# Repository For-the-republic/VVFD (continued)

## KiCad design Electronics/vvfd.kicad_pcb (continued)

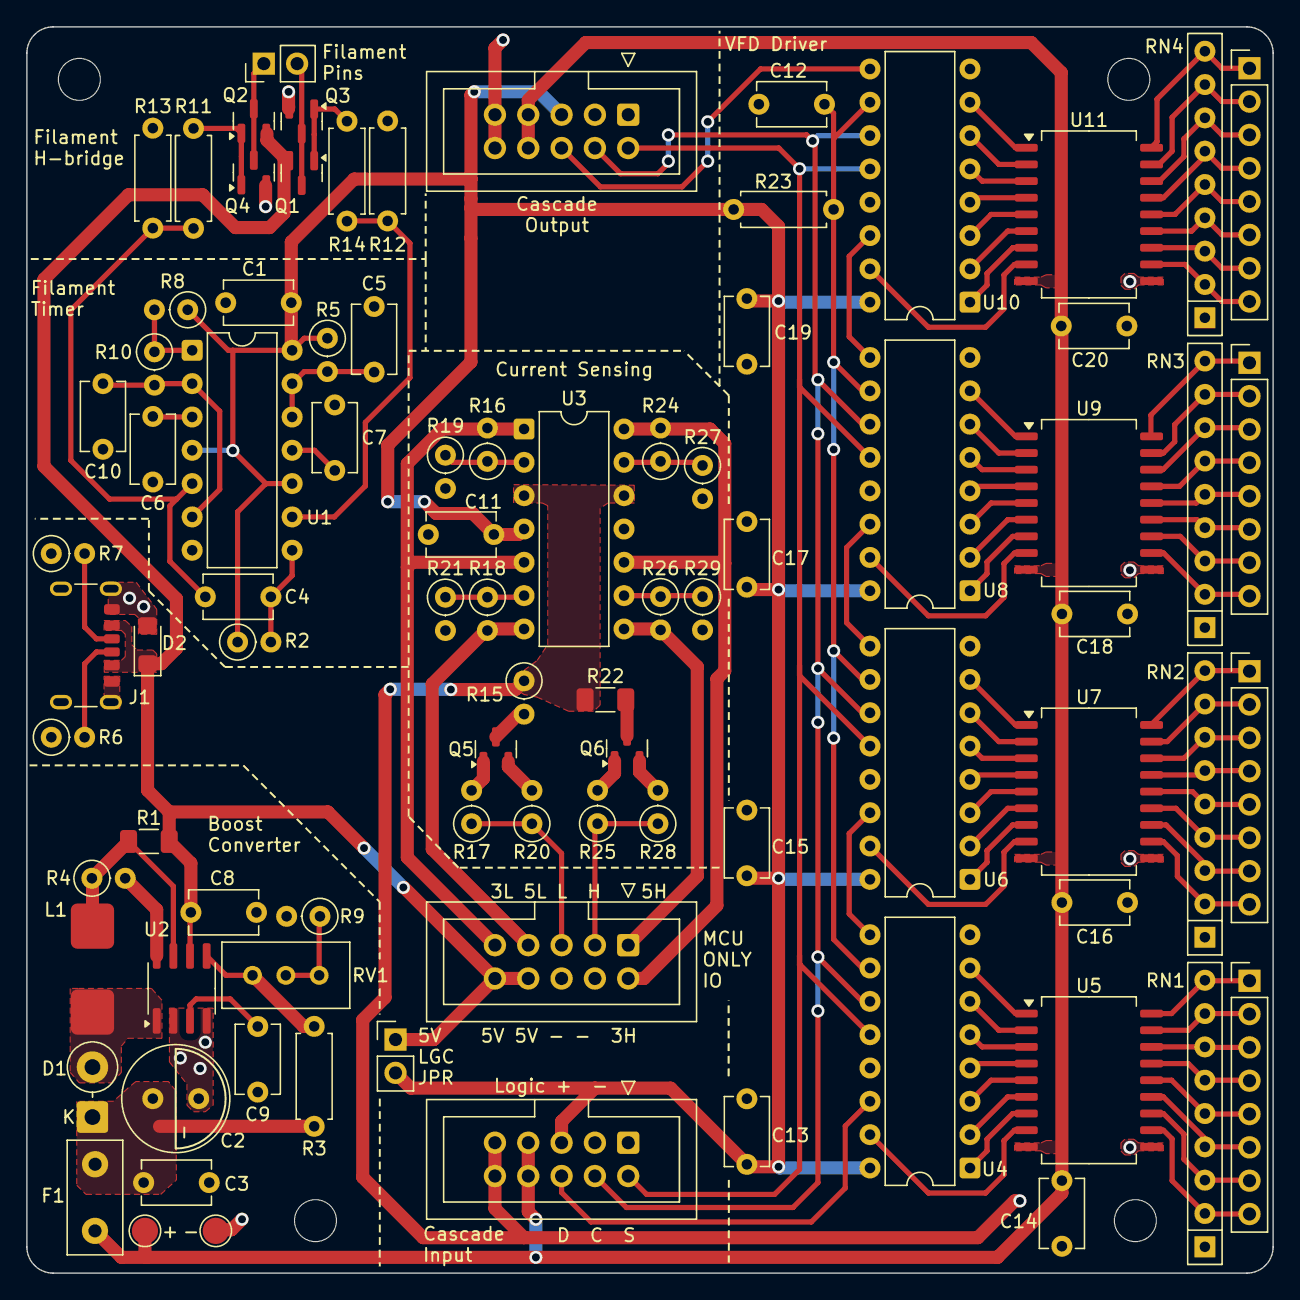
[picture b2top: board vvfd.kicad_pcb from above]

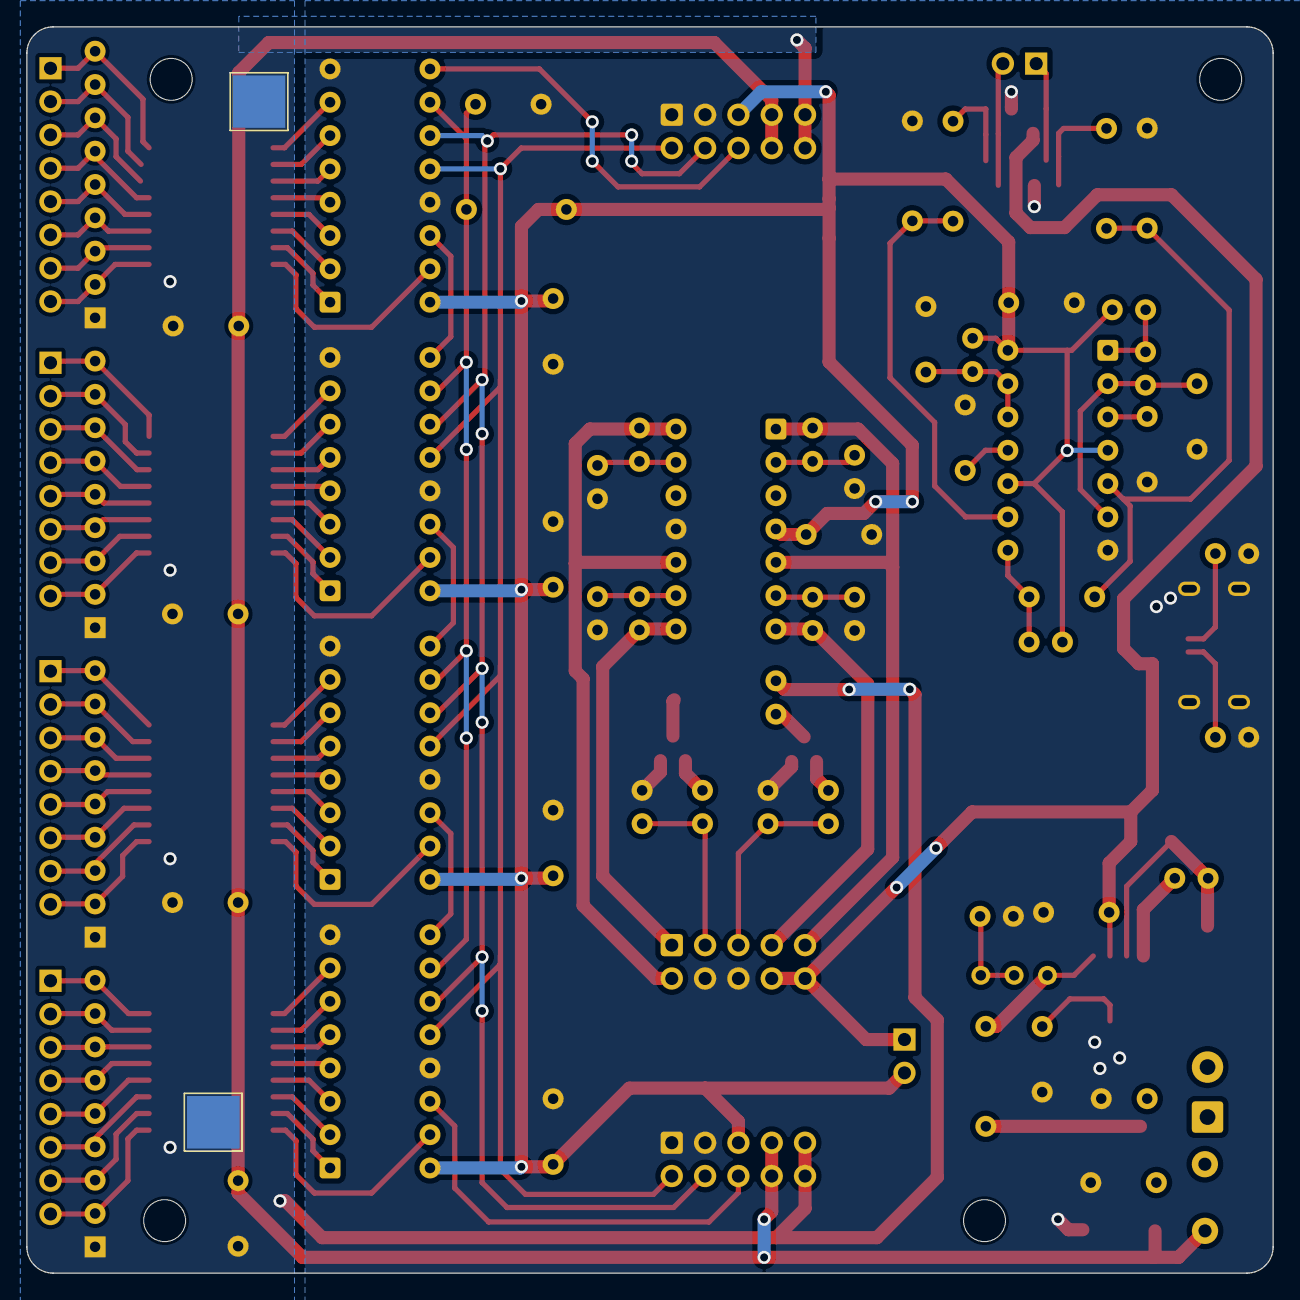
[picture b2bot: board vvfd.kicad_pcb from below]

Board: 2 copper layers, 95.0 x 95.0 mm, 93 parts (2 on the bottom side), 112 nets.

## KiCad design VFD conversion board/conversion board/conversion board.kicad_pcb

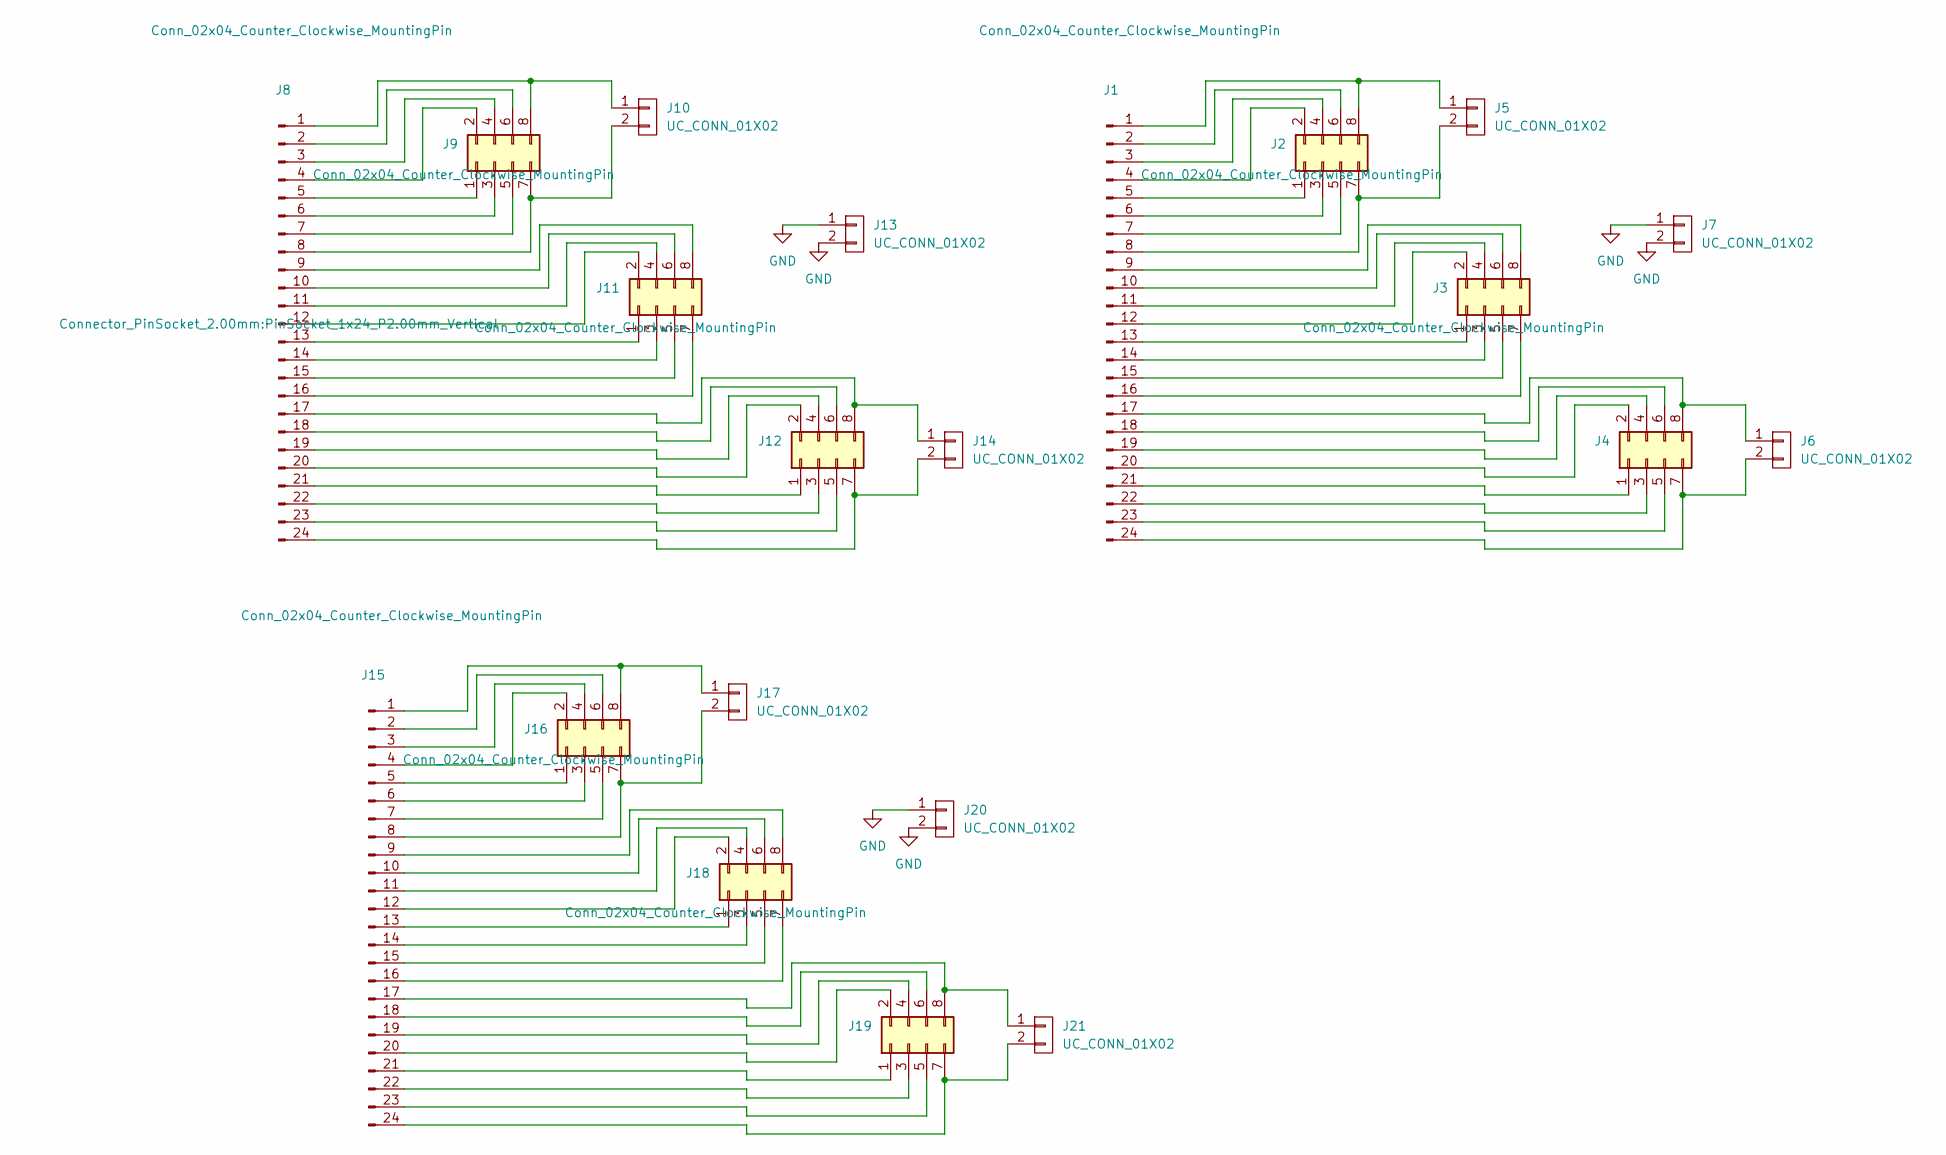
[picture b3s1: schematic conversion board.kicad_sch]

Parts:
J1, J8, J15: Conn_01x24_Pin; PinSocket_1x24_P2.00mm_Vertical
J2, J3, J4, J9, J11, J12, J16, J18, J19: Conn_02x04_Counter_Clockwise_MountingPin; PinHeader_2x04_P2.54mm_Vertical
J5, J6, J7, J10, J13, J14, J17, J20, J21: UC_CONN_01X02; PinHeader_1x02_P2.54mm_Vertical

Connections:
GND: J7.1, J7.2, J13.1, J13.2, J20.1, J20.2
unnamed: J1.1, J2.8, J5.1
unnamed: J1.2, J2.6
unnamed: J1.3, J2.4
unnamed: J1.4, J2.2
unnamed: J1.5, J2.1
unnamed: J1.6, J2.3
unnamed: J1.7, J2.5
unnamed: J1.8, J2.7, J5.2
unnamed: J1.9, J3.8
unnamed: J1.10, J3.6
unnamed: J1.11, J3.4
unnamed: J1.12, J3.2
unnamed: J1.13, J3.1
unnamed: J1.14, J3.3
unnamed: J1.15, J3.5
unnamed: J1.16, J3.7
unnamed: J1.17, J4.8, J6.1
unnamed: J1.18, J4.6
unnamed: J1.19, J4.4
unnamed: J1.20, J4.2
unnamed: J1.21, J4.1
unnamed: J1.22, J4.3
unnamed: J1.23, J4.5
unnamed: J1.24, J4.7, J6.2
unnamed: J8.2, J9.6
unnamed: J8.3, J9.4
unnamed: J8.4, J9.2
unnamed: J8.5, J9.1
unnamed: J8.6, J9.3
unnamed: J8.7, J9.5
unnamed: J8.1, J9.8, J10.1
unnamed: J8.8, J9.7, J10.2
unnamed: J8.13, J11.1
unnamed: J8.12, J11.2
unnamed: J8.14, J11.3
unnamed: J8.11, J11.4
unnamed: J8.15, J11.5
unnamed: J8.10, J11.6
unnamed: J8.16, J11.7
unnamed: J8.9, J11.8
unnamed: J8.21, J12.1
unnamed: J8.20, J12.2
unnamed: J8.22, J12.3
unnamed: J8.19, J12.4
unnamed: J8.23, J12.5
unnamed: J8.18, J12.6
unnamed: J8.24, J12.7, J14.2
unnamed: J8.17, J12.8, J14.1
unnamed: J15.1, J16.8, J17.1
unnamed: J15.2, J16.6
unnamed: J15.3, J16.4
unnamed: J15.4, J16.2
unnamed: J15.5, J16.1
unnamed: J15.6, J16.3
unnamed: J15.7, J16.5
unnamed: J15.8, J16.7, J17.2
unnamed: J15.9, J18.8
unnamed: J15.10, J18.6
unnamed: J15.11, J18.4
unnamed: J15.12, J18.2
unnamed: J15.13, J18.1
unnamed: J15.14, J18.3
unnamed: J15.15, J18.5
unnamed: J15.16, J18.7
unnamed: J15.17, J19.8, J21.1
unnamed: J15.18, J19.6
unnamed: J15.19, J19.4
unnamed: J15.20, J19.2
unnamed: J15.21, J19.1
unnamed: J15.22, J19.3
unnamed: J15.23, J19.5
unnamed: J15.24, J19.7, J21.2

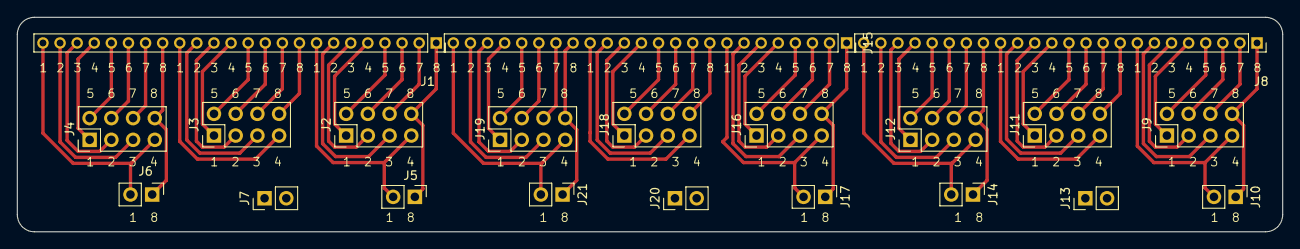
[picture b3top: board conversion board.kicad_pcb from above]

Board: 2 copper layers, 148.0 x 25.1 mm, 21 parts (0 on the bottom side), 73 nets.

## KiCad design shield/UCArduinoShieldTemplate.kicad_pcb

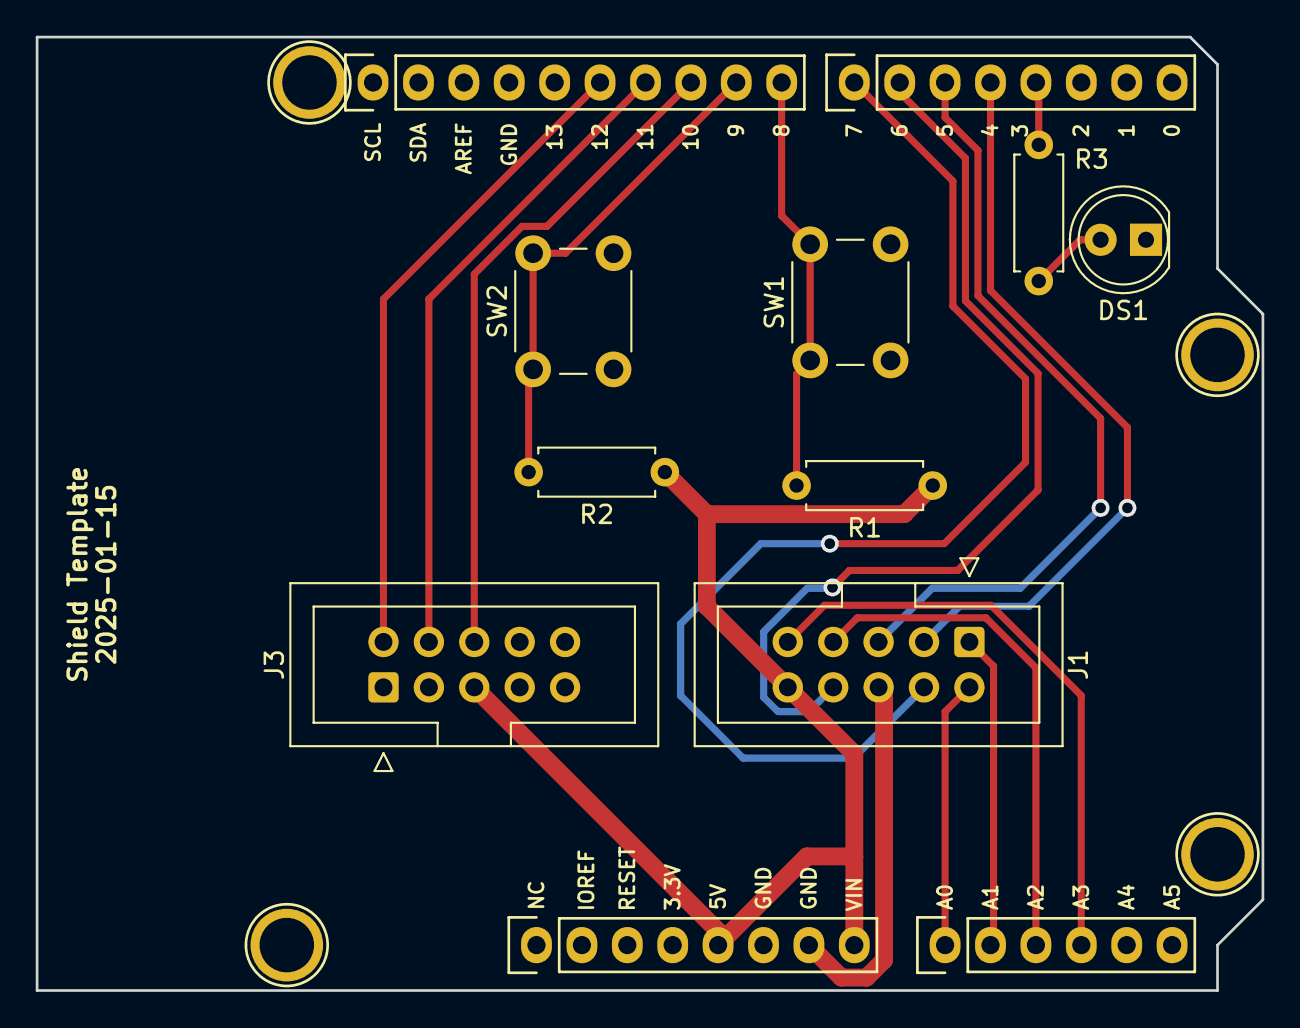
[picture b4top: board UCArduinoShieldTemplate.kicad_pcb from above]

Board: 2 copper layers, 68.6 x 53.3 mm, 16 parts (0 on the bottom side), 17 nets.

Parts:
DS1: UC_LED; LED_D5.0mm
H1, H2, H3, H4: CONN_01X01; Mounting_Hole
J1, J3: Conn_02x05_Counter_Clockwise; IDC-Header_2x05_P2.54mm_Vertical
P1: Power; Socket_Strip_Arduino_1x08
P2: Analog; Socket_Strip_Arduino_1x06
P3: Digital; Socket_Strip_Arduino_1x10
P4: Digital; Socket_Strip_Arduino_1x08
R1, R2, R3: 1k; R_Axial_DIN0207_L6.3mm_D2.5mm_P7.62mm_Horizontal
SW1, SW2: UC_SW_Push; SW_PUSH_6mm_H5mm

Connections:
3HCS: J1.2, P2.1
3LCS: J1.9, P2.4
5HCS: J1.1, P2.2
5LCS: J1.7, P2.3
+5V: J1.10, J3.5, P1.5, P1.8, R1.1, R2.1
BONE: P3.10, R1.2, SW1.1
BTWO: P3.9, R2.2, SW2.1
CLK: J3.4, P3.7
GND: DS1.1 (K), J1.6, J3.1, J3.3, P1.6, P1.7, P3.4, SW1.2, SW2.2
H1: J1.8, P4.2
H2: J1.4, P4.1
HCS_EN: J1.3, P4.4
LCS_EN: J1.5, P4.3
MAIN_SER_OUT: J3.6, P3.8
unnamed: DS1.2 (A), R3.2
SYNC: J3.2, P3.6
indicator: P4.5, R3.1

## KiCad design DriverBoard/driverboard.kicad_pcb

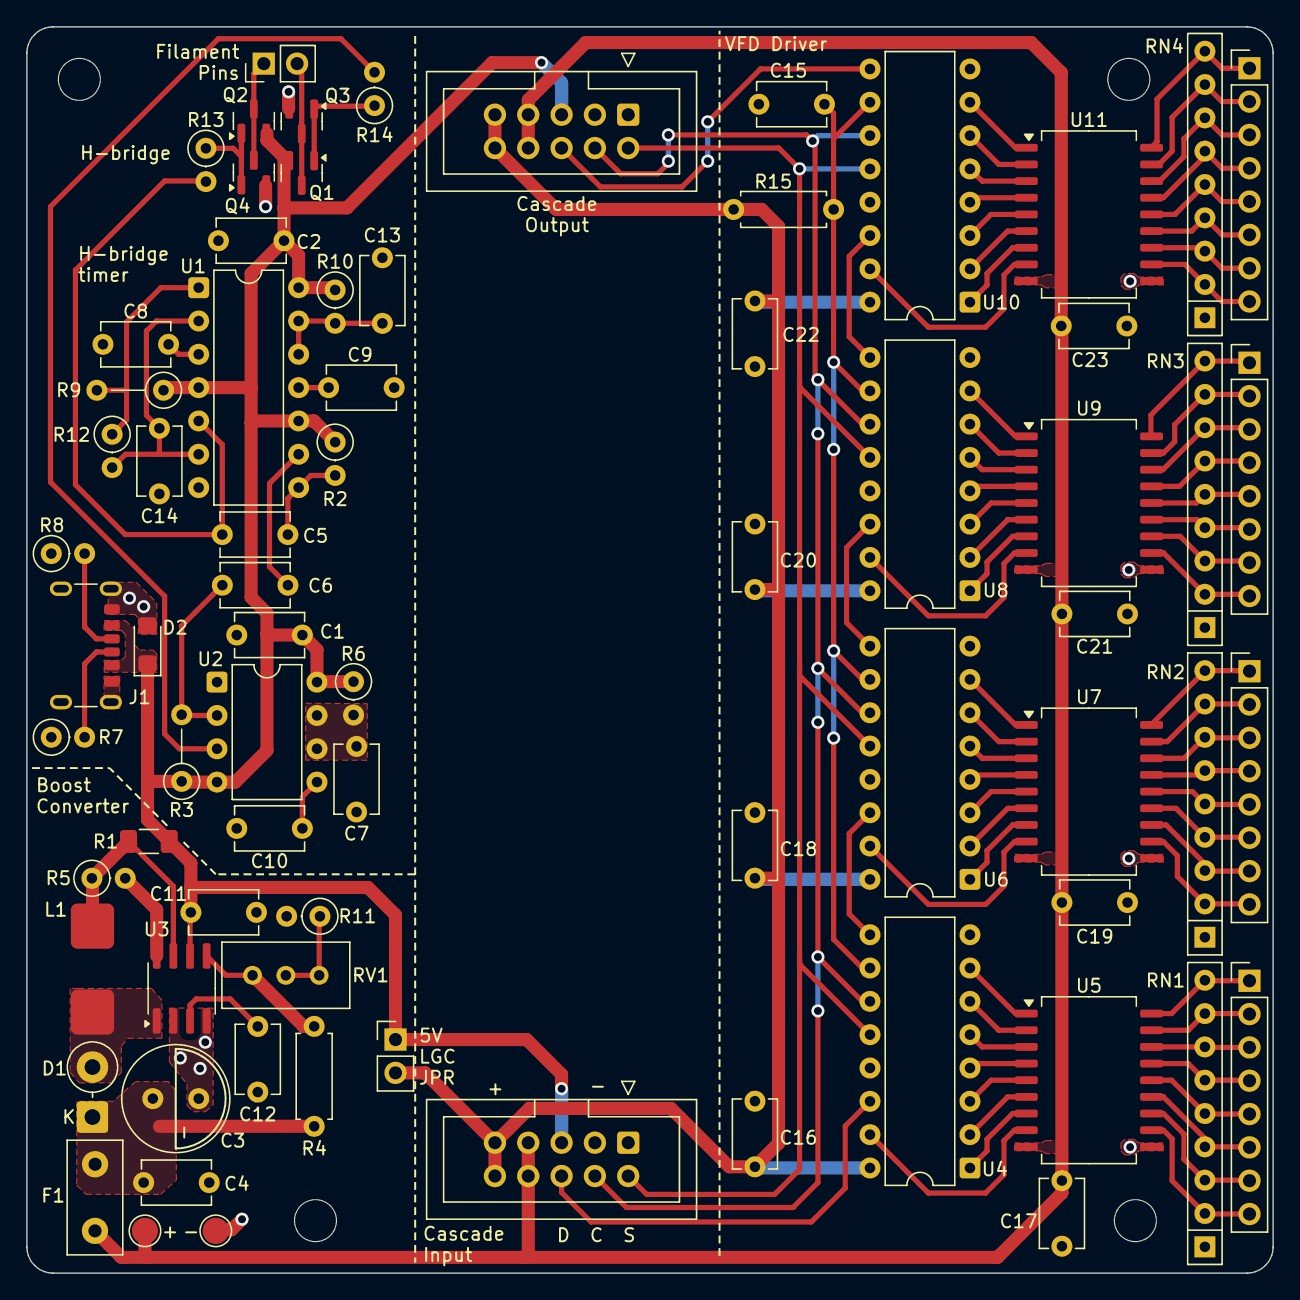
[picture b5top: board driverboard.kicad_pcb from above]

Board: 2 copper layers, 95.0 x 95.0 mm, 77 parts (0 on the bottom side), 101 nets.

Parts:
C1, C2, C4, C11, C15, C16, C17, C18, C19, C20, C21, C22, C23: 100n; C_Disc_D5.1mm_W3.2mm_P5.00mm
C3: 100u; C_Radial_D8.0mm_H11.5mm_P3.50mm
C5, C6, C8, C9, C10, C13: 10n; C_Disc_D5.1mm_W3.2mm_P5.00mm
C7, C14: 220n; C_Disc_D5.1mm_W3.2mm_P5.00mm
C12: 330p; C_Disc_D5.1mm_W3.2mm_P5.00mm
D1: SB240L; D_DO-15_P3.81mm_Vertical_KathodeUp
D2: SMF5V0A; D_SMF
F1: 100mA hold; Fuse_Littelfuse_395Series
H1, H2, H3, H4: MountingHole; MountingHole_3.2mm_M3
J1: USB_C_Receptacle_USB2.0_14P; USB_C_Receptacle_GCT_USB4125-xx-x-0190_6P_TopMnt_Horizontal
J2: Conn_01x02_Pin; PinHeader_1x02_P2.54mm_Vertical
J3, J4: Conn_02x05_Counter_Clockwise; IDC-Header_2x05_P2.54mm_Vertical
J5, J6, J7, J8: Conn_01x08_Pin; PinHeader_1x08_P2.54mm_Vertical
JP1: Jumper_2_Open; PinHeader_1x02_P2.54mm_Vertical
L1: 100uH; SPM7054VT-D
Q1, Q2: DMG2305UX; SOT-23
Q3, Q4: SL3402; SOT-23
R1: 0.2R; R_1206_3216Metric_Pad1.30x1.75mm_HandSolder
R2: 3k3; R_Axial_DIN0207_L6.3mm_D2.5mm_P2.54mm_Vertical
R3: 3k3; R_Axial_DIN0207_L6.3mm_D2.5mm_P5.08mm_Vertical
R4: 100k; R_Axial_DIN0207_L6.3mm_D2.5mm_P7.62mm_Horizontal
R5: 180R; R_Axial_DIN0207_L6.3mm_D2.5mm_P2.54mm_Vertical
R6: 39k; R_Axial_DIN0207_L6.3mm_D2.5mm_P2.54mm_Vertical
R7, R8: 5k1; R_Axial_DIN0207_L6.3mm_D2.5mm_P2.54mm_Vertical
R9: 1k; R_Axial_DIN0207_L6.3mm_D2.5mm_P5.08mm_Vertical
R10: 10k; R_Axial_DIN0207_L6.3mm_D2.5mm_P2.54mm_Vertical
R11: 3k9; R_Axial_DIN0207_L6.3mm_D2.5mm_P2.54mm_Vertical
R12: 68k; R_Axial_DIN0207_L6.3mm_D2.5mm_P2.54mm_Vertical
R13, R14: 2K2; R_Axial_DIN0207_L6.3mm_D2.5mm_P2.54mm_Vertical
R15: 10k; R_Axial_DIN0207_L6.3mm_D2.5mm_P7.62mm_Horizontal
RN1, RN2, RN3, RN4: 1M; R_Array_SIP9
RV1: 10k; Potentiometer_Bourns_3296W_Vertical
TP1, TP2: TestPoint; TestPoint_Pad_D2.0mm
U1: LM556; DIP-14_W7.62mm
U2: LM555xN; DIP-8_W7.62mm
U3: MC34063AD; SOIC-8_3.9x4.9mm_P1.27mm
U4, U6, U8, U10: 74HC595; DIP-16_W7.62mm
U5, U7, U9, U11: TBD62783A; SOP-18_7x12.5mm_P1.27mm

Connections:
+5V: C1.1, C2.1, C11.1, D2.1 (A1), J1.A9 (VBUS), J1.B9 (VBUS), J3.5, J4.5, JP1.1 (A), Q1.2 (S), Q2.2 (S), R1.1, R2.1, R3.1, R6.1, R9.1, R10.1, U1.4 (R), U1.10 (R), U1.14 (VCC), U2.4 (R), U2.8 (VCC), U3.6 (Vin)
/BOOST_OUT: C3.1, C4.1, D1.1 (K), F1.2, R4.1
/BOOST_SW: D1.2 (A), L1.2, U3.1 (SwC)
/DRIVE_COLLECTOR: R5.2, U3.8 (DC)
/IL_SENSE: L1.1, R1.2, R5.1, U3.7 (Ipk)
/POT: R11.1, RV1.2, RV1.3
/SER_CHAIN1: U4.9 (QH'), U6.14 (SER)
/SER_CHAIN2: U6.9 (QH'), U8.14 (SER)
/SER_CHAIN3: U8.9 (QH'), U10.14 (SER)
/TC: C12.1, U3.3 (TC)
/TIMING_CAP_1: C14.1, R12.2, U1.2 (THR), U1.6 (TR)
/TIMING_CAP_2: C13.1, R10.2, U1.12 (THR), U1.13 (DIS)
/TIMING_CAP_3: C7.1, R6.2, U2.6 (THR), U2.7 (DIS)
/TIM_1_CV: C8.1, U1.3 (CV)
/TIM_1_DIS: R9.2, R12.1, U1.1 (DIS)
/TIM_2_CV: C9.1, U1.11 (CV)
/TIM_2_IN: C5.2, R2.2, U1.8 (TR)
/TIM_2_OUT: C6.1, U1.9 (Q)
/TIM_3_CV: C10.1, U2.5 (CV)
/TIM_3_IN: C6.2, R3.2, U2.2 (TR)
/VFD drive 1/A: U4.15 (QA), U5.8 (I8)
/VFD drive 1/B: U4.1 (QB), U5.7 (I7)
/VFD drive 1/C: U4.2 (QC), U5.6 (I6)
/VFD drive 1/D: U4.3 (QD), U5.5 (I5)
/VFD drive 1/E: U4.4 (QE), U5.4 (I4)
/VFD drive 1/F: U4.5 (QF), U5.3 (I3)
/VFD drive 1/G: U4.6 (QG), U5.2 (I2)
/VFD drive 1/H: U4.7 (QH), U5.1 (I1)
/VFD drive 2/A: U6.15 (QA), U7.8 (I8)
/VFD drive 2/B: U6.1 (QB), U7.7 (I7)
/VFD drive 2/C: U6.2 (QC), U7.6 (I6)
/VFD drive 2/D: U6.3 (QD), U7.5 (I5)
/VFD drive 2/E: U6.4 (QE), U7.4 (I4)
/VFD drive 2/F: U6.5 (QF), U7.3 (I3)
/VFD drive 2/G: U6.6 (QG), U7.2 (I2)
/VFD drive 2/H: U6.7 (QH), U7.1 (I1)
/VFD drive 3/A: U8.15 (QA), U9.8 (I8)
/VFD drive 3/B: U8.1 (QB), U9.7 (I7)
/VFD drive 3/C: U8.2 (QC), U9.6 (I6)
/VFD drive 3/D: U8.3 (QD), U9.5 (I5)
/VFD drive 3/E: U8.4 (QE), U9.4 (I4)
/VFD drive 3/F: U8.5 (QF), U9.3 (I3)
/VFD drive 3/G: U8.6 (QG), U9.2 (I2)
/VFD drive 3/H: U8.7 (QH), U9.1 (I1)
/VFD drive 4/A: U10.15 (QA), U11.8 (I8)
/VFD drive 4/B: U10.1 (QB), U11.7 (I7)
/VFD drive 4/C: U10.2 (QC), U11.6 (I6)
/VFD drive 4/D: U10.3 (QD), U11.5 (I5)
/VFD drive 4/E: U10.4 (QE), U11.4 (I4)
/VFD drive 4/F: U10.5 (QF), U11.3 (I3)
/VFD drive 4/G: U10.6 (QG), U11.2 (I2)
/VFD drive 4/H: U10.7 (QH), U11.1 (I1)
BRIDGE_G1: Q2.1 (G), Q4.1 (G), R13.1
BRIDGE_G2: Q1.1 (G), Q3.1 (G), R14.1
CLK: J3.4, J4.4, U4.11 (SRCLK), U6.11 (SRCLK), U8.11 (SRCLK), U10.11 (SRCLK)
CLR: C15.1, R15.1, U4.10 (~SRCLR), U6.10 (~SRCLR), U8.10 (~SRCLR), U10.10 (~SRCLR)
FILAMENT_1: J2.2, Q1.3 (D), Q3.3 (D)
FILAMENT_2: J2.1, Q2.3 (D), Q4.3 (D)
GND: C1.2, C2.2, C3.2, C4.2, C7.2, C8.2, C9.2, C10.2, C11.2, C12.2, C13.2, C14.2, C15.2, C16.2, C17.2, C18.2, C19.2, C20.2, C21.2, C22.2, C23.2, D2.2 (A2), J1.A12 (GND), J1.B12 (GND), J1.S1 (SHIELD), J3.1, J3.3, J4.1, J4.3, Q3.2 (S), Q4.2 (S), R7.1, R8.1, R11.2, RN1.1 (common), RN2.1 (common), RN3.1 (common), RN4.1 (common), TP1.1, U1.7 (GND), U2.1 (GND), U3.2 (SwE), U3.4 (GND), U4.8 (GND), U4.13 (~OE), U5.10 (GND), U6.8 (GND), U6.13 (~OE), U7.10 (GND), U8.8 (GND), U8.13 (~OE), U9.10 (GND), U10.8 (GND), U10.13 (~OE), U11.10 (GND)
H1: C5.1, R13.2, U1.5 (Q)
H2: R14.2, U2.3 (Q)
MAIN_SER_IN: J4.6, U4.14 (SER)
MAIN_SER_OUT: J3.6, U10.9 (QH')
unnamed: J1.A5 (CC1), R8.2
unnamed: J1.B5 (CC2), R7.2
unnamed: J5.1, RN1.9 (R8), U5.18 (O1)
unnamed: J5.2, RN1.8 (R7), U5.17 (O2)
unnamed: J5.3, RN1.7 (R6), U5.16 (O3)
unnamed: J5.4, RN1.6 (R5), U5.15 (O4)
unnamed: J5.5, RN1.5 (R4), U5.14 (O5)
unnamed: J5.6, RN1.4 (R3), U5.13 (O6)
unnamed: J5.7, RN1.3 (R2), U5.12 (O7)
unnamed: J5.8, RN1.2 (R1), U5.11 (O8)
unnamed: J6.1, RN2.9 (R8), U7.18 (O1)
unnamed: J6.2, RN2.8 (R7), U7.17 (O2)
unnamed: J6.3, RN2.7 (R6), U7.16 (O3)
unnamed: J6.4, RN2.6 (R5), U7.15 (O4)
unnamed: J6.5, RN2.5 (R4), U7.14 (O5)
unnamed: J6.6, RN2.4 (R3), U7.13 (O6)
unnamed: J6.7, RN2.3 (R2), U7.12 (O7)
unnamed: J6.8, RN2.2 (R1), U7.11 (O8)
unnamed: J7.1, RN3.9 (R8), U9.18 (O1)
unnamed: J7.2, RN3.8 (R7), U9.17 (O2)
unnamed: J7.3, RN3.7 (R6), U9.16 (O3)
unnamed: J7.4, RN3.6 (R5), U9.15 (O4)
unnamed: J7.5, RN3.5 (R4), U9.14 (O5)
unnamed: J7.6, RN3.4 (R3), U9.13 (O6)
unnamed: J7.7, RN3.3 (R2), U9.12 (O7)
unnamed: J7.8, RN3.2 (R1), U9.11 (O8)
unnamed: J8.1, RN4.9 (R8), U11.18 (O1)
unnamed: J8.2, RN4.8 (R7), U11.17 (O2)
unnamed: J8.3, RN4.7 (R6), U11.16 (O3)
unnamed: J8.4, RN4.6 (R5), U11.15 (O4)
unnamed: J8.5, RN4.5 (R4), U11.14 (O5)
unnamed: J8.6, RN4.4 (R3), U11.13 (O6)
unnamed: J8.7, RN4.3 (R2), U11.12 (O7)
unnamed: J8.8, RN4.2 (R1), U11.11 (O8)
SYNC: J3.2, J4.2, U4.12 (RCLK), U6.12 (RCLK), U8.12 (RCLK), U10.12 (RCLK)
VCC: C16.1, C18.1, C20.1, C22.1, J3.9, J3.10, J4.9, J4.10, JP1.2 (B), R15.2, U4.16 (VCC), U6.16 (VCC), U8.16 (VCC), U10.16 (VCC)
VDC: C17.1, C19.1, C21.1, C23.1, F1.1, J3.7, J3.8, J4.7, J4.8, TP2.1, U5.9 (VCC), U7.9 (VCC), U9.9 (VCC), U11.9 (VCC)
V_FB: R4.2, RV1.1, U3.5 (Vfb)

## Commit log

2025-08-25 Update README.md
    added the porper readme
2025-08-26 add electronics directory
2025-08-26 Fixed ERC and DRC
2025-08-26 Fix cascade IDC connector
    The cascade input and output IDC pins didn't correspond before
2025-08-27 updated readme
    made a more completer readme for the users to understand
2025-08-27 made a shield extension for the ardiuno uno board
    ditto
2025-08-28 added the unos code
    added what should be a basic working version of the arduino unos code.
2025-08-28 bug fixes
    the code now builds properly
2025-08-28 added some more functions to the shifting system
    added some more functions and cleaned it up a bit
2025-09-01 Added filament timer
    Added a timer to control the filament h-brdige on the main PCB.
    Also added some more decoupling capacitors, but some have dubious
    placement. Still better than nothing.
2025-09-01 added some stuff for bad apple
    ditto
2025-09-03 added conversion kit
    added a conversion kit and some light code adding
2025-09-04 Added VFD output pulldowns
    Added pulldowns and more decoupling capacitors. The capacitors and
    pulldowns can probably be omitted, but I've put them in for more flexibility.
2025-09-07 Fixed H-bridge
    Old H-bridge was the wrong type, changed to using some P-channel
    mosfets. Also fixed the cost spreadsheet.
2025-09-08 Added timer circuit test picture
    Added a picture of the timer circuits output recorded on an oscilloscope
2025-09-14 Updated BOM
    Updated BOMs because some of the component prices changed and a part
    went out of stock.
2025-09-16 readme redo
    redid the readme and added some other things
2025-09-17 Prepared driverboard for export
2025-09-18 Minor PCB rev
    Moved shift register bypass caps around a bit. Also changed a price on
    the BOM, that's the final change before the digikey parts order is in.
2025-09-29 added bad apple
    bad apple
2025-10-02 99% there
    ditto
2025-10-03 Fixed H-bridge timer
    The H-bridge timer had no blank time on a clock transition before, this
    would cause a momentary short circuit as the mosfet switching times
    aren't instant. To fix this an extra 555 timer stage was added.
2025-10-04 vfd
    vfd image processing now works for 16x8 videos
2025-10-05 pad apple working fully
    DO NOT TOUCH THE MAIN CODE
2025-10-05 Updated shield
    Also made driver board a bit tider
2025-10-05 Added current sensing demo
    Added that and useful debugging code to a new folder.
    Sam can use the parts he need or delete it in the future.
2025-10-07 Update README.md
    video of it working added to readme
2025-10-08 Removed Current Sensing
    Removed current sensing, because it would require a major design
    overhaul to work properly.
